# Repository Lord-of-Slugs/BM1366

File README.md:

## BM1366
- The BM1366 is a undocumented SHA256 mining ASIC from Bitmain. It's used in the Antminer S19XP and the S19k Pro
- Bitmain claims the BM1366 has 0.021J/GH efficiency
- The BM1366 is available (new) for around $15 each in small quantities.
- The BM1366 has a different footprint and pinout from the BM1397 and BM1387 in previous bitaxe.
- The BM1366 appears to roll more than just the nonce on the chip. This is great news, because it allows much longer serial chains of ASICs and new work doesn't need to be sent as often.

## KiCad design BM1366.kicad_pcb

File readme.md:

## BM1366
- BM1366 is an undocumented SHA256 ASIC from Bitmain.
- It is used in the Antminer S19XP and the S19k Pro.
- Bitmain claims the BM1366 has 0.021J/GH efficiency.
- The BM1366 is available for around $15 each in small quantities.

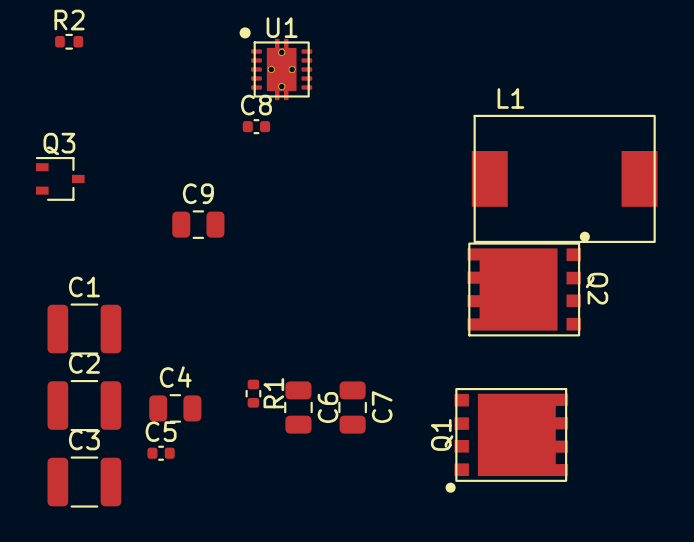
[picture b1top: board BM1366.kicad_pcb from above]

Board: 2 copper layers, 16 parts (0 on the bottom side), 12 nets, no tracks yet.

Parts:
C1, C2, C3: 47uF; C_1210_3225Metric
C4: 1uF; C_0805_2012Metric
C5: 3.3nF; C_0402_1005Metric
C6: 1.5nF; C_0805_2012Metric
C7: 180pF; C_0805_2012Metric
C8: 0.1uF; C_0402_1005Metric
C9: 10uF; C_0805_2012Metric
L1: 150nH; FP1005R1-R15-R
Q1, Q2: CSD17311Q5; CSD17576Q5B
Q3: 2N7002K; SOT-323_SC-70
R1: 3.83k; R_0402_1005Metric
R2: 4.12k; R_0402_1005Metric
U1: TPS4030x

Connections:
Earth: C1.2, C2.2, C3.2, C4.2, C5.1, C9.2, Q3.2 (S), R2.2, U1.11 (GND)
unnamed: C6.2, R1.1
unnamed: C1.1, C2.1, C3.1, C4.1, Q1.5 (D), U1.1 (VDD)
unnamed: Q1.4 (G), U1.7 (HDRV)
unnamed: C8.2, L1.1, Q1.1, Q1.2, Q1.3 (S), Q2.5 (D), U1.8 (SW)
unnamed: Q2.4 (G), R2.1, U1.9 (LDRV)
unnamed: Q2.1, Q2.2, Q2.3 (S)
unnamed: C5.2, Q3.3 (D), U1.2 (EN/SS)
unnamed: C8.1, U1.6 (BOOT)
unnamed: C9.1, U1.10 (BP)
unnamed: C6.1, C7.2, U1.4 (COMP)
unnamed: C7.1, R1.2, U1.5 (FB)

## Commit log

2024-06-08 updated .gitignore
2024-06-08 did some things
2024-06-08 did some stuffs
